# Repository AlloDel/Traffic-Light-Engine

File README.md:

# Traffic-Light-Engine
A traffc light engine

PDF and images of schematic and 3d render in /docs directory

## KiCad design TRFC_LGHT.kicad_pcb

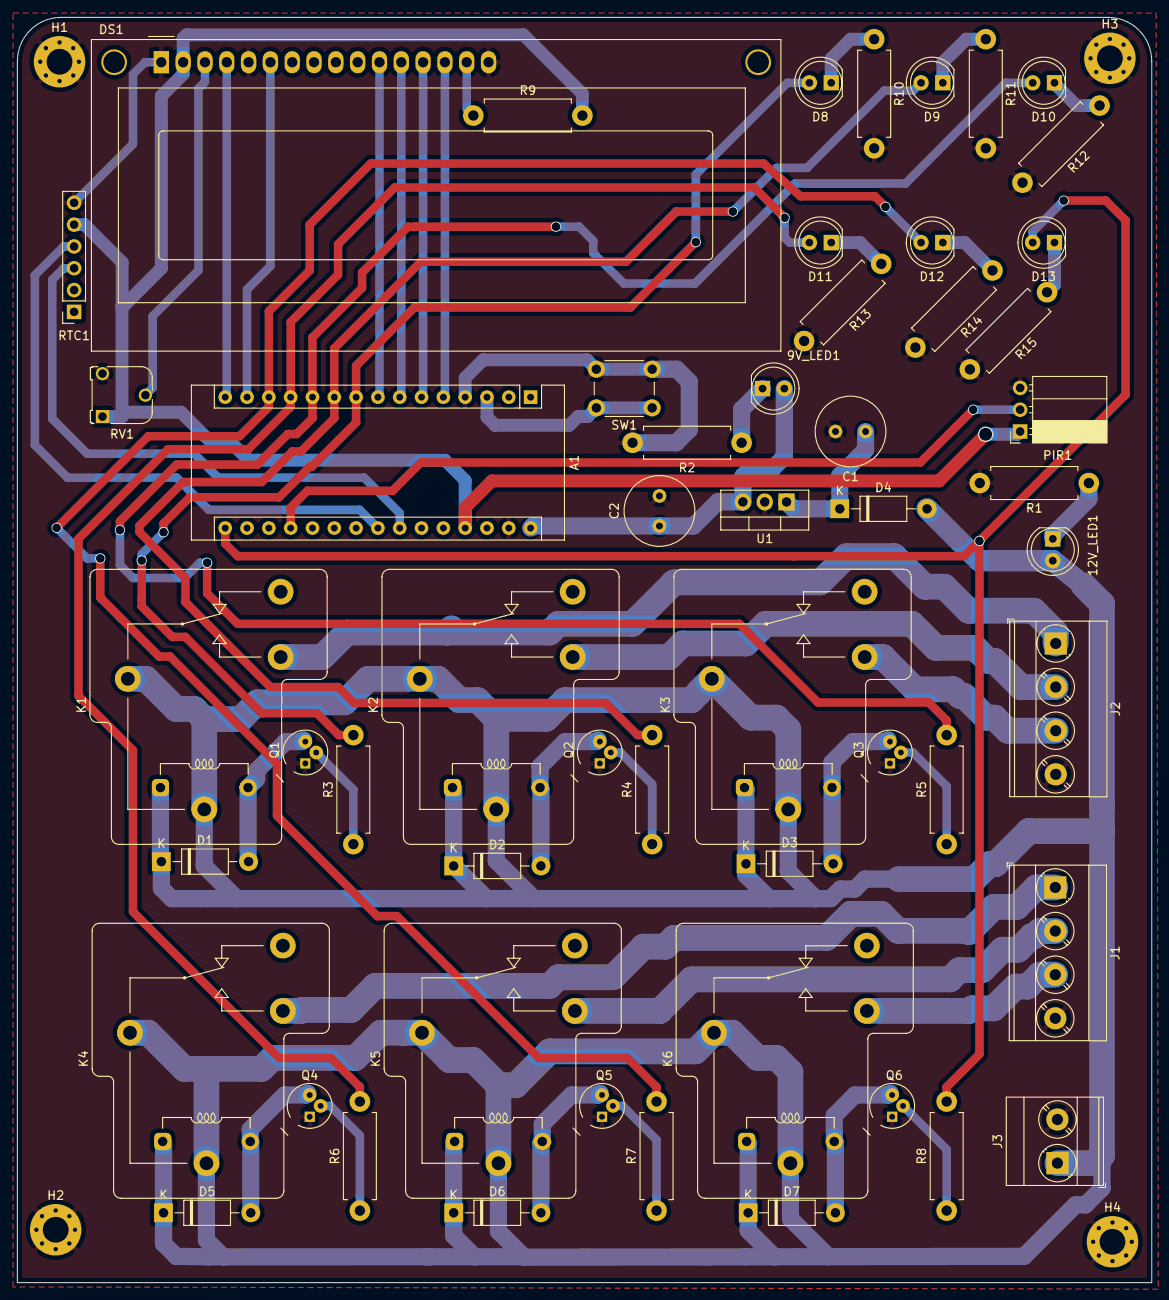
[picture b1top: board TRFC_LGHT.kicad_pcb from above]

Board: 2 copper layers, 132.1 x 147.3 mm, 58 parts (0 on the bottom side), 49 nets.

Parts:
9V_LED1, 12V_LED1: LED_Small; LED_D5.0mm_Clear
A1: Arduino_Nano_v3.x; Arduino_Nano
C1, C2: C_Small; C_Radial_D8.0mm_H11.5mm_P3.50mm
D1, D2, D3, D4, D5, D6, D7: 1N4007; D_DO-41_SOD81_P10.16mm_Horizontal
D8, D9, D10, D11, D12, D13: LED_Small; LED_D5.0mm_Clear
DS1: WC1602A
H1, H2, H3, H4: MountingHole_Pad; MountingHole_3mm_Pad_Via
J1, J2: Conn_01x04_Female; TerminalBlock_Phoenix_MKDS-3-4-5.08_1x04_P5.08mm_Horizontal
J3: Conn_01x02_Female; TerminalBlock_Phoenix_MKDS-3-2-5.08_1x02_P5.08mm_Horizontal
K1, K2, K3, K4, K5, K6: RAYEX-L90; Relay_SPDT_RAYEX-L90
PIR1: Conn_01x03_Female; PinSocket_1x03_P2.54mm_Horizontal
Q1, Q2, Q3, Q4, Q5, Q6: 2N2222A; TO-18-3
R1, R2: 1k; R_Axial_DIN0411_L9.9mm_D3.6mm_P12.70mm_Horizontal
R3, R4, R5, R6, R7, R8: 2.2k; R_Axial_DIN0411_L9.9mm_D3.6mm_P12.70mm_Horizontal
R9: 220; R_Axial_DIN0411_L9.9mm_D3.6mm_P12.70mm_Horizontal
R10, R11, R12, R13, R14, R15: 330; R_Axial_DIN0411_L9.9mm_D3.6mm_P12.70mm_Horizontal
RTC1: Conn_01x06_Female; PinSocket_1x06_P2.54mm_Vertical
RV1: R_POT_10k; Potentiometer_Runtron_RM-065_Vertical
SW1: SW_Push; SW_PUSH_6mm_H13mm
U1: L7809; TO-220-3_Vertical

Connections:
+5V: A1.27, DS1.2, PIR1.1, R9.2, RTC1.5, RV1.1
+9V: 9V_LED1.2, A1.30, C2.1, U1.3
/AMBER_1: J2.2, K2.14
/AMBER_2: J1.2, K5.14
/GREEN_1: J2.3, K3.14
/GREEN_2: J1.3, K6.14
/INPUT_1: A1.9, D8.2, R3.2
/INPUT_2: A1.10, D9.2, R4.2
/INPUT_3: A1.11, D10.2, R5.2
/INPUT_4: A1.12, D11.2, R6.2
/INPUT_5: A1.13, D12.2, R7.2
/INPUT_6: A1.16, D13.2, R8.2
/LCD_VO: DS1.3, RV1.2
/PIR_OUTPUT: A1.19, PIR1.2
/RED_1: J2.1, K1.14
/RED_2: J1.1, K4.14
/SCL: A1.24, RTC1.3
/SDA: A1.23, RTC1.4
/pin2: A1.5, DS1.14
/pin3: A1.6, DS1.13
/pin4: A1.7, DS1.12
/pin5: A1.8, DS1.11
/pin11: A1.14, DS1.6
/pin12: A1.15, DS1.4
GND: A1.4, A1.29, C1.2, C2.2, DS1.1, DS1.5, DS1.16, H1.1, H2.1, H3.1, H4.1, J1.4, J2.4, J3.2, PIR1.3, Q1.1, Q2.1, Q3.1, Q4.1, Q5.1, Q6.1, R1.2, R2.2, R10.2, R11.2, R12.2, R13.2, R14.2, R15.2, RTC1.6, RV1.3, SW1.2, U1.2
unnamed: 9V_LED1.1, R2.1
unnamed: 12V_LED1.1, R1.1
unnamed: A1.3, SW1.1
unnamed: C1.1, D4.1, U1.1
unnamed: D1.2, K1.A2, Q1.3
unnamed: D2.2, K2.A2, Q2.3
unnamed: D3.2, K3.A2, Q3.3
unnamed: D5.2, K4.A2, Q4.3
unnamed: D6.2, K5.A2, Q5.3
unnamed: D7.2, K6.A2, Q6.3
unnamed: D8.1, R10.1
unnamed: D9.1, R11.1
unnamed: D10.1, R12.1
unnamed: D11.1, R13.1
unnamed: D12.1, R14.1
unnamed: D13.1, R15.1
unnamed: DS1.15, R9.1
unnamed: Q1.2, R3.1
unnamed: Q2.2, R4.1
unnamed: Q3.2, R5.1
unnamed: Q4.2, R6.1
unnamed: Q5.2, R7.1
unnamed: Q6.2, R8.1
VCC: 12V_LED1.2, D1.1, D2.1, D3.1, D4.2, D5.1, D6.1, D7.1, J3.1, K1.11A, K1.11B, K1.A1, K2.11A, K2.11B, K2.A1, K3.11A, K3.11B, K3.A1, K4.11A, K4.11B, K4.A1, K5.11A, K5.11B, K5.A1, K6.11A, K6.11B, K6.A1
